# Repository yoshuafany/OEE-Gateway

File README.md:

# OEE-Gateway
Komponen :
-RASPBERRY PI 3
-RESISTOR 1k ohm
-RESISTOT 3k ohm
-ANALOG TO I2C CONVERTER ADC 4CH ADS1115
-DC-DC STEP-DOWN LM2596

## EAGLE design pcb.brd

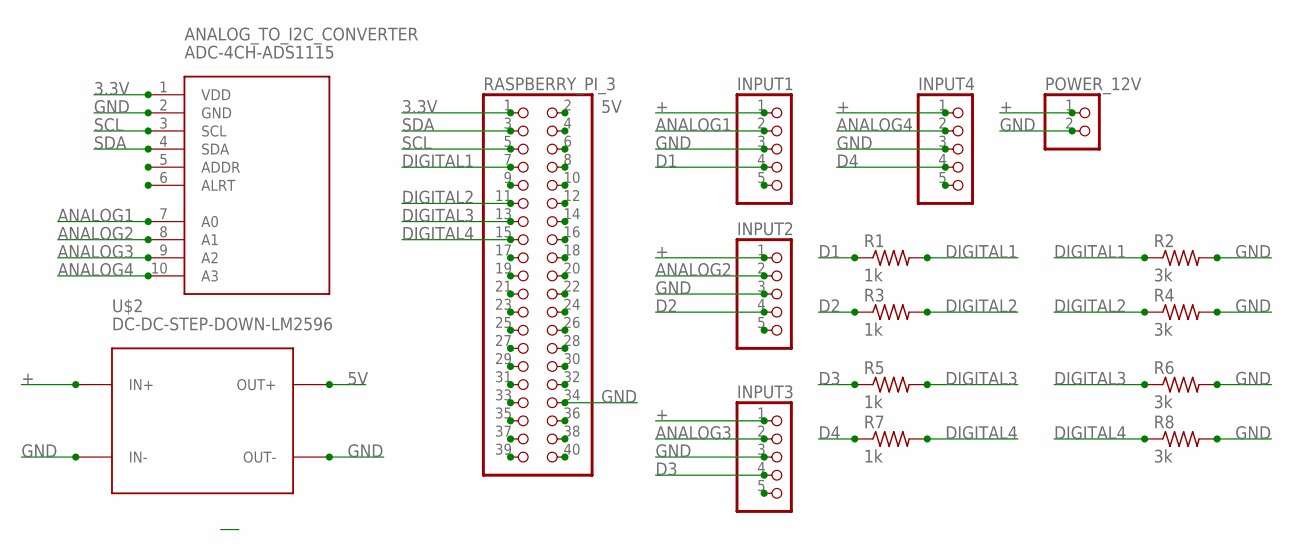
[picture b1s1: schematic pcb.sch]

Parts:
ANALOG_TO_I2C_CONVERTER: ADC-4CH-ADS1115
INPUT1, INPUT2, INPUT3, INPUT4: PINHD-1X5; 1X05
POWER_12V: PINHD-1X2; 1X02
R1, R3, R5, R7: 1k; 0207/12
R2, R4, R6, R8: 3k; 0207/12
RASPBERRY_PI_3: PINHD-2X20; 2X20
U$2: DC-DC-STEP-DOWN-LM2596

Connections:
3.3V: ANALOG_TO_I2C_CONVERTER.1 (VDD), RASPBERRY_PI_3.1
5V: RASPBERRY_PI_3.2, U$2.OUT+
+: INPUT1.1, INPUT2.1, INPUT3.1, INPUT4.1, POWER_12V.1, U$2.IN+
ANALOG1: ANALOG_TO_I2C_CONVERTER.7 (A0), INPUT1.2
ANALOG2: ANALOG_TO_I2C_CONVERTER.8 (A1), INPUT2.2
ANALOG3: ANALOG_TO_I2C_CONVERTER.9 (A2), INPUT3.2
ANALOG4: ANALOG_TO_I2C_CONVERTER.10 (A3), INPUT4.2
D1: INPUT1.4, R1.1
D2: INPUT2.4, R3.1
D3: INPUT3.4, R5.1
D4: INPUT4.4, R7.1
DIGITAL1: R1.2, R2.1, RASPBERRY_PI_3.7
DIGITAL2: R3.2, R4.1, RASPBERRY_PI_3.11
DIGITAL3: R5.2, R6.1, RASPBERRY_PI_3.13
DIGITAL4: R7.2, R8.1, RASPBERRY_PI_3.15
GND: ANALOG_TO_I2C_CONVERTER.2 (GND), INPUT1.3, INPUT2.3, INPUT3.3, INPUT4.3, POWER_12V.2, R2.2, R4.2, R6.2, R8.2, RASPBERRY_PI_3.34, U$2.IN-, U$2.OUT-
SCL: ANALOG_TO_I2C_CONVERTER.3 (SCL), RASPBERRY_PI_3.5
SDA: ANALOG_TO_I2C_CONVERTER.4 (SDA), RASPBERRY_PI_3.3

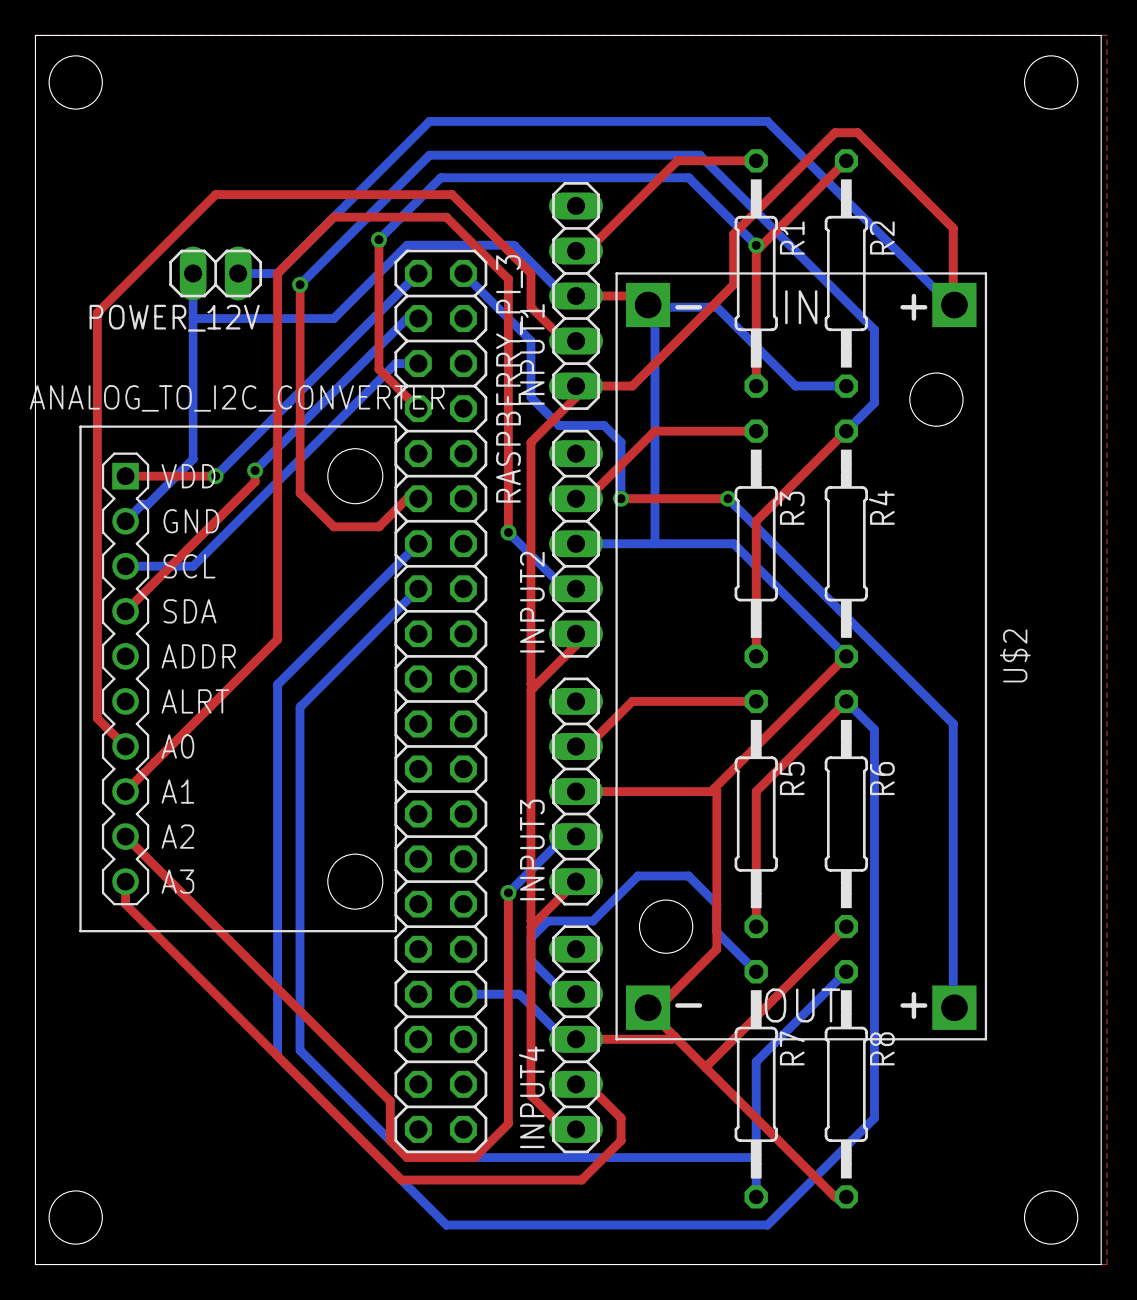
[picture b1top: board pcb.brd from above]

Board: 2 copper layers, 60.1 x 69.3 mm, 16 parts (0 on the bottom side), 18 nets.

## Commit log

2020-04-15 remove pcb.brd
2020-04-15 remove pcb.sch
2020-04-15 design
2020-04-17 remove file

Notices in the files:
parts and their libraries:
diy-modules: Released under the Creative Commons Attribution 4.0 International License: http://creativecommons.org/licenses/by/4.0
